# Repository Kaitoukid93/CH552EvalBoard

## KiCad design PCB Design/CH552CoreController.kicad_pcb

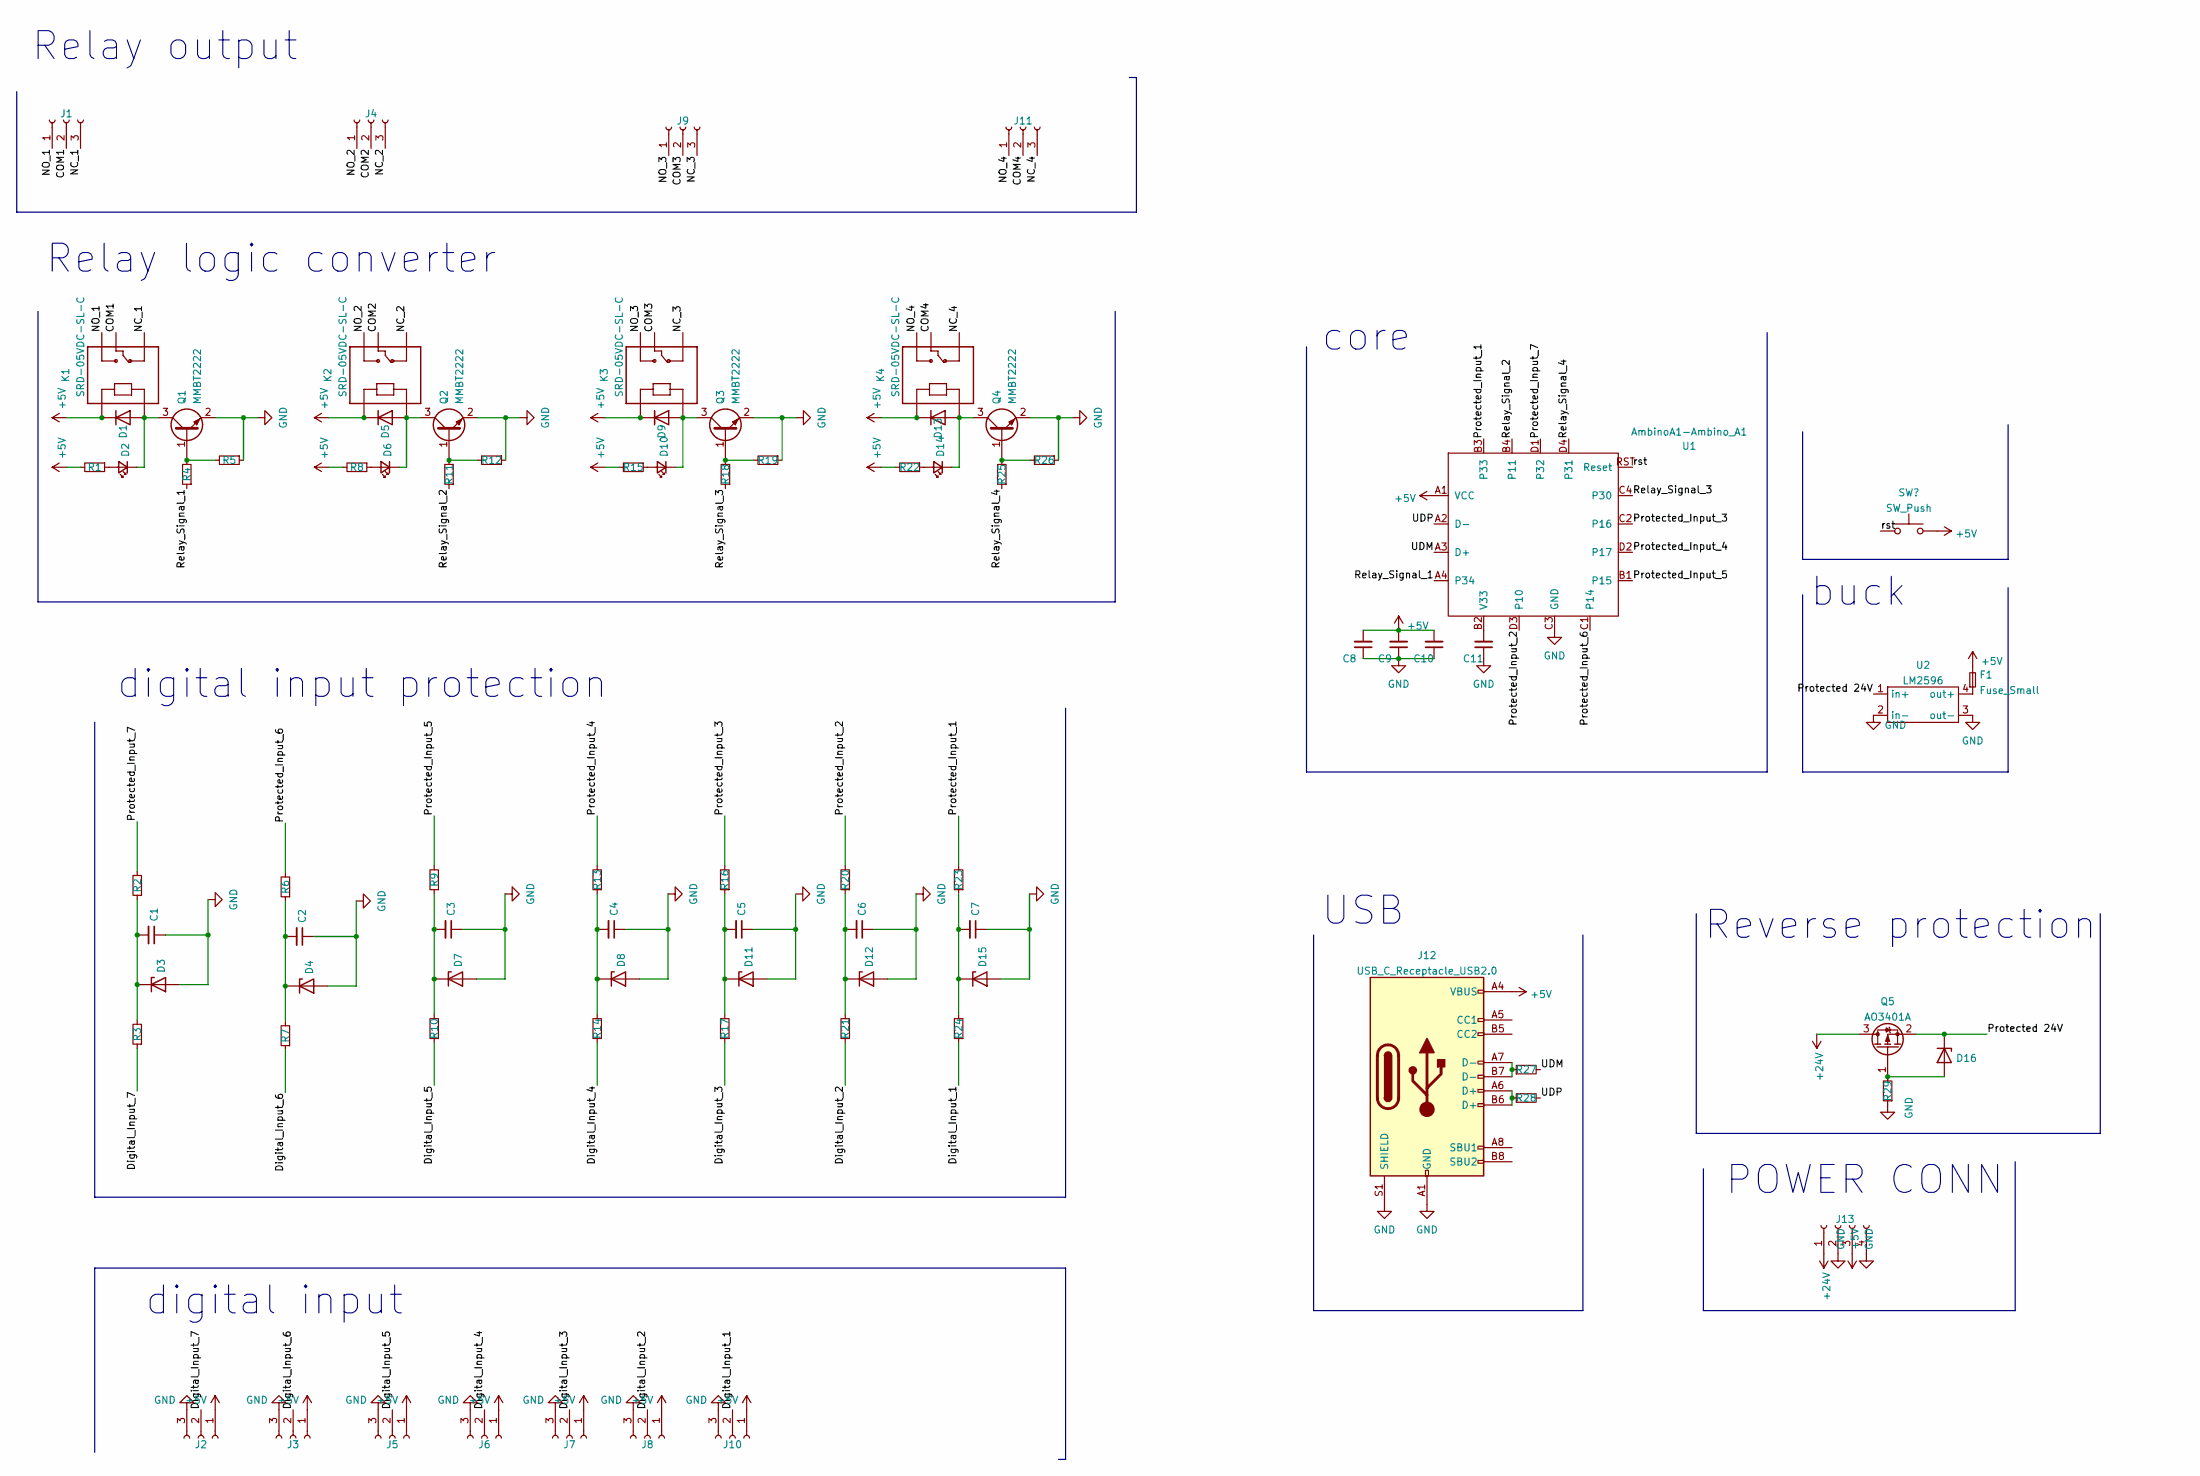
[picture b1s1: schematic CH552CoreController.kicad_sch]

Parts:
C1, C2, C3, C4, C5, C6, C7, C10, C11: 104; C_0805_2012Metric
C8: 105; C_0805_2012Metric
C9: 106; C_0805_2012Metric
D1, D5, D9, D13: 1N4148; D_SOD-123
D2, D6, D10, D14: LED_RED; LED_0805_2012Metric
D3: BZT52C5V6 5.6V zener; D_SOD-123
D4, D7, D8, D11, D12, D15: D_Zener; D_SOD-123
D16: BZT52C10; D_SOD-123
F1: Fuse_Small; Fuse_1210_3225Metric
J1, J2, J3, J4, J5, J6, J7, J8, J9, J10, J11: Conn_01x03_Female; PhoenixContact_MSTBA_2,5_3-G-5,08_1x03_P5.08mm_Horizontal
J12: USB_C_Receptacle_USB2.0; USB_C_Receptacle_HRO_TYPE-C-31-M-12
J13: Conn_01x04_Female; PhoenixContact_MSTBA_2,5_4-G-5,08_1x04_P5.08mm_Horizontal
K1, K2, K3, K4: SRD-05VDC-SL-C; RELAY_SRD-05VDC-SL-C
Q1, Q2, Q3, Q4: MMBT2222; SOT-23
Q5: AO3401A; SOP-8_3.9x4.9mm_P1.27mm
R1, R4, R8, R11, R15, R18, R22, R25: 1K; R_0805_2012Metric
R2, R3, R6, R7, R9, R10, R13, R14, R16, R17, R20, R21, R23, R24: 4k7; R_0805_2012Metric
R5, R12, R19, R26: 10K; R_0805_2012Metric
R27, R28: R_Small; R_0805_2012Metric
R29: 100k; R_0805_2012Metric
U1: AmbinoA1-Ambino_A1; BGA-16_4x4_11.0x11.0mm
U2: LM2596; LM2596 module

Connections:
+5V: C8.2, C9.2, C10.2, D1.1 (K), D5.1 (K), D9.1 (K), D13.1 (K), F1.2, J2.1, J3.1, J5.1, J6.1, J7.1, J8.1, J10.1, J12.A4 (VBUS), J12.A9 (VBUS), J12.B4 (VBUS), J12.B9 (VBUS), J13.3, K1.A1, K2.A1, K3.A1, K4.A1, R1.2, R8.2, R15.2, R22.2, U1.A1 (VCC); also elsewhere on the board
+24V: J13.1, Q5.3 (D)
/COM1: J1.2, K1.COM
/COM2: J4.2, K2.COM
/COM3: J9.2, K3.COM
/COM4: J11.2, K4.COM
/Digital_Input_1: J10.2, R24.1
/Digital_Input_2: J8.2, R21.1
/Digital_Input_3: J7.2, R17.1
/Digital_Input_4: J6.2, R14.1
/Digital_Input_5: J5.2, R10.1
/Digital_Input_6: J3.2, R7.1
/Digital_Input_7: J2.2, R3.1
/NC_1: J1.3, K1.NC
/NC_2: J4.3, K2.NC
/NC_3: J9.3, K3.NC
/NC_4: J11.3, K4.NC
/NO_1: J1.1, K1.NO
/NO_2: J4.1, K2.NO
/NO_3: J9.1, K3.NO
/NO_4: J11.1, K4.NO
/Protected 24V: D16.1 (K), Q5.2 (S), U2.1 (in+)
/Protected_Input_1: R23.2, U1.B3 (P33)
/Protected_Input_2: R20.2, U1.D3 (P10)
/Protected_Input_3: R16.2, U1.C2 (P16)
/Protected_Input_4: R13.2, U1.D2 (P17)
/Protected_Input_5: R9.2, U1.B1 (P15)
/Protected_Input_6: R6.2, U1.C1 (P14)
/Protected_Input_7: R2.2, U1.D1 (P32)
/Relay_Signal_1: R4.1, U1.A4 (P34)
/Relay_Signal_2: R11.1, U1.B4 (P11)
/Relay_Signal_3: R18.1, U1.C4 (P30)
/Relay_Signal_4: R25.1, U1.D4 (P31)
/UDM: R27.2, U1.A3 (D+)
/UDP: R28.2, U1.A2 (D-)
/rst: U1.RST (Reset); also elsewhere on the board
GND: C1.1, C2.1, C3.1, C4.1, C5.1, C6.1, C7.1, C8.1, C9.1, C10.1, C11.1, D3.2 (A), D4.2 (A), D7.2 (A), D8.2 (A), D11.2 (A), D12.2 (A), D15.2 (A), J2.3, J3.3, J5.3, J6.3, J7.3, J8.3, J10.3, J12.A1 (GND), J12.A12 (GND), J12.B1 (GND), J12.B12 (GND), J12.S1 (SHIELD), J13.2, J13.4, Q1.2 (E), Q2.2 (E), Q3.2 (E), Q4.2 (E), R5.1, R12.1, R19.1, R26.1, R29.1, U1.C3 (GND), U2.2 (in-), U2.3 (out-)
unnamed: C1.2, D3.1 (K), R2.1, R3.2
unnamed: C2.2, D4.1 (K), R6.1, R7.2
unnamed: C3.2, D7.1 (K), R9.1, R10.2
unnamed: C4.2, D8.1 (K), R13.1, R14.2
unnamed: C5.2, D11.1 (K), R16.1, R17.2
unnamed: C6.2, D12.1 (K), R20.1, R21.2
unnamed: C7.2, D15.1 (K), R23.1, R24.2
unnamed: C11.2, U1.B2 (V33)
unnamed: D1.2 (A), D2.1 (K), K1.A2, Q1.3 (C)
unnamed: D2.2 (A), R1.1
unnamed: D5.2 (A), D6.1 (K), K2.A2, Q2.3 (C)
unnamed: D6.2 (A), R8.1
unnamed: D9.2 (A), D10.1 (K), K3.A2, Q3.3 (C)
unnamed: D10.2 (A), R15.1
unnamed: D13.2 (A), D14.1 (K), K4.A2, Q4.3 (C)
unnamed: D14.2 (A), R22.1
unnamed: D16.2 (A), Q5.1 (G), R29.2
unnamed: F1.1, U2.4 (out+)
unnamed: J12.A6 (D+), J12.B6 (D+), R28.1
unnamed: J12.A7 (D-), J12.B7 (D-), R27.1
unnamed: Q1.1 (B), R4.2, R5.2
unnamed: Q2.1 (B), R11.2, R12.2
unnamed: Q3.1 (B), R18.2, R19.2
unnamed: Q4.1 (B), R25.2, R26.2

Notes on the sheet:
buck
Reverse protection
POWER CONN
USB
digital input protection
Relay logic converter
digital input
core
Relay output

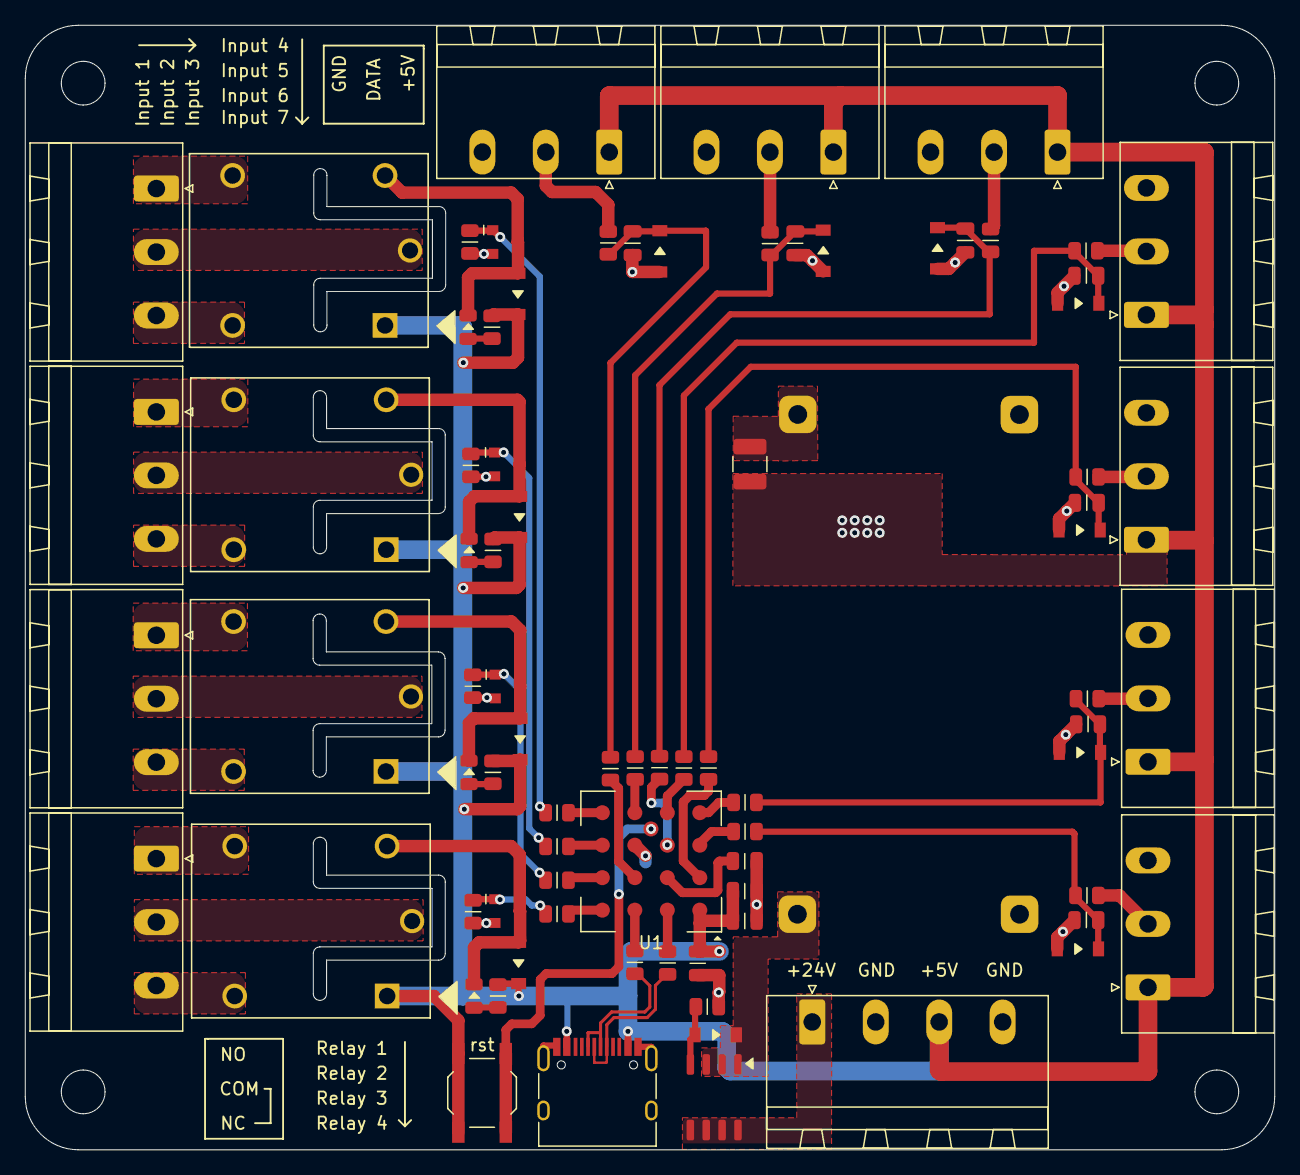
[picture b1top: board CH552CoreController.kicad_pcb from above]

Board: 2 copper layers, 100.0 x 90.0 mm, 82 parts (0 on the bottom side), 61 nets.

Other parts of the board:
SW1: SW_Push; SW_SPST_TL3342

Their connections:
+5V: SW1.1; also elsewhere on the board
/rst: SW1.2; also elsewhere on the board

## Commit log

2022-02-11 init()
2022-02-11 add button
